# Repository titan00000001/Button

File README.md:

# Player

Ever Wanted to just play with a bunch on sensors with LEDs all in the shape of a cute creature

## Schematic
.png)

## PCB
.png)
.png)

## Features
- 3 LEDs
- Light Based LED
- switch controlled LED
- Adjustable LED

## How to build
Just order the PCB & components, open up the KiCAD file and build it accordingly.

## BOM
- 1 Battery_Cell
- 3 LEDS
- 2 Resistors
- 1 Potentiometer
- 1 Button
- 1 Photoresistor

Made by `@vinay nori` on slack :D

Made as a part of http://solder.hackclub.com/!

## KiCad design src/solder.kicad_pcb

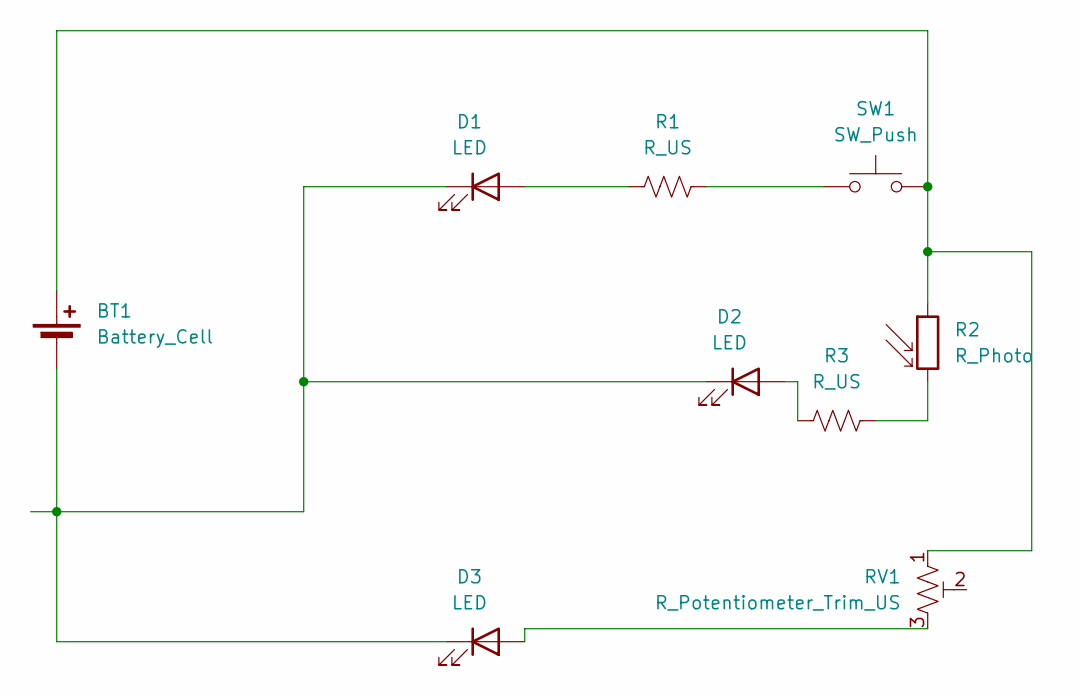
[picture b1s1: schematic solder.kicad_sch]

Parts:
BT1: Battery_Cell; BatteryHolder_Keystone_3034_1x20mm
D1, D2, D3: LED; LED_D3.0mm
R1: R_US; R_Axial_DIN0207_L6.3mm_D2.5mm_P7.62mm_Horizontal
R2: R_Photo; R_LDR_5.1x4.3mm_P3.4mm_Vertical
R3: R_US; R_Axial_DIN0204_L3.6mm_D1.6mm_P7.62mm_Horizontal
RV1: R_Potentiometer_Trim_US; Potentiometer_Vishay_T73YP_Vertical
SW1: SW_Push; SW_PUSH_6mm

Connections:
unnamed: BT1.1 (+), R2.1, RV1.1, SW1.2
unnamed: BT1.2 (-), D1.1 (K), D2.1 (K), D3.1 (K)
unnamed: D1.2 (A), R1.1
unnamed: D2.2 (A), R3.1
unnamed: D3.2 (A), RV1.3
unnamed: R1.2, SW1.1
unnamed: R2.2, R3.2

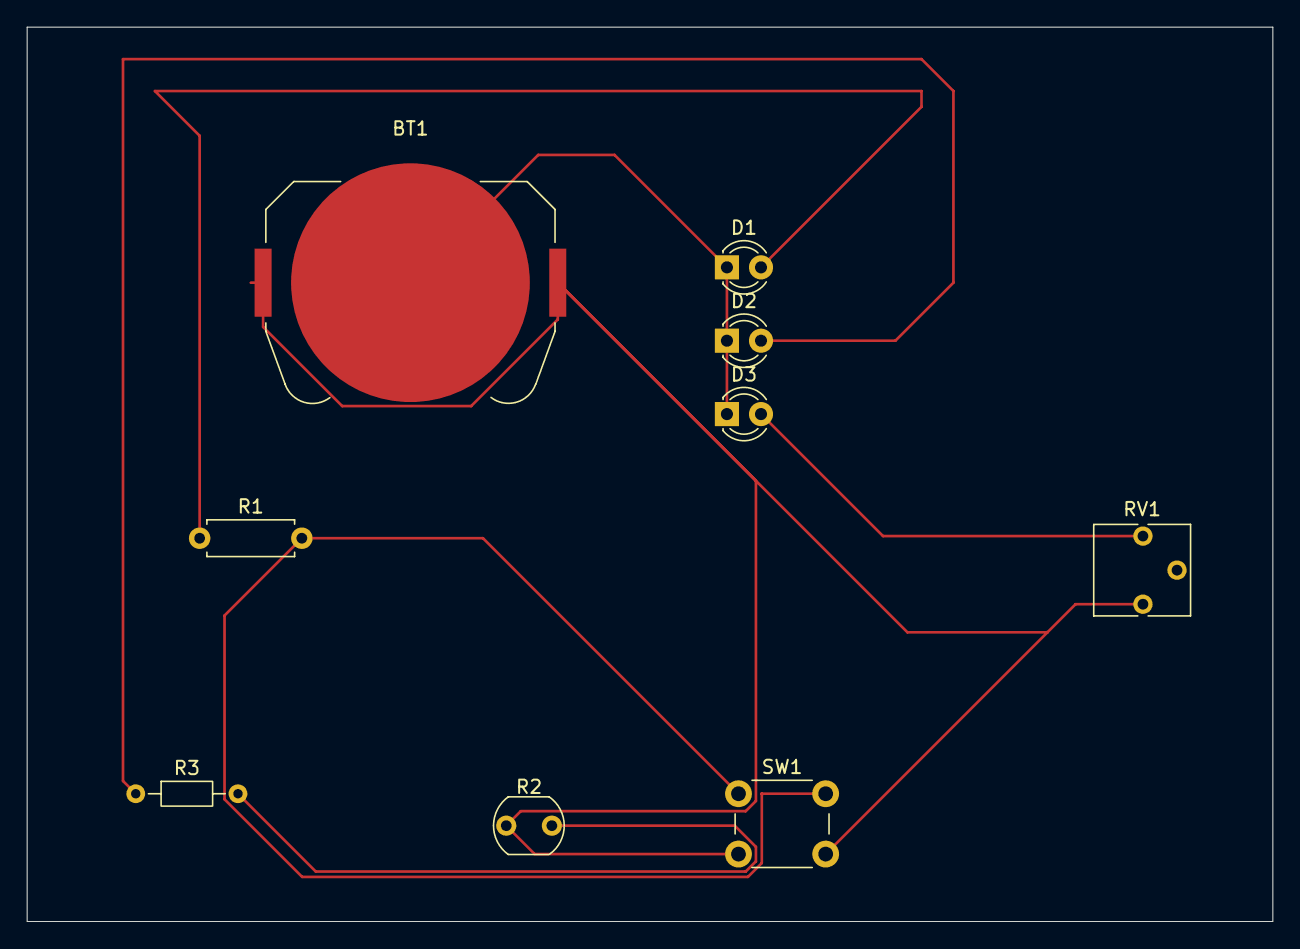
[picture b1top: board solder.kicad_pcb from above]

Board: 2 copper layers, 92.9 x 66.7 mm, 9 parts (0 on the bottom side), 7 nets.
